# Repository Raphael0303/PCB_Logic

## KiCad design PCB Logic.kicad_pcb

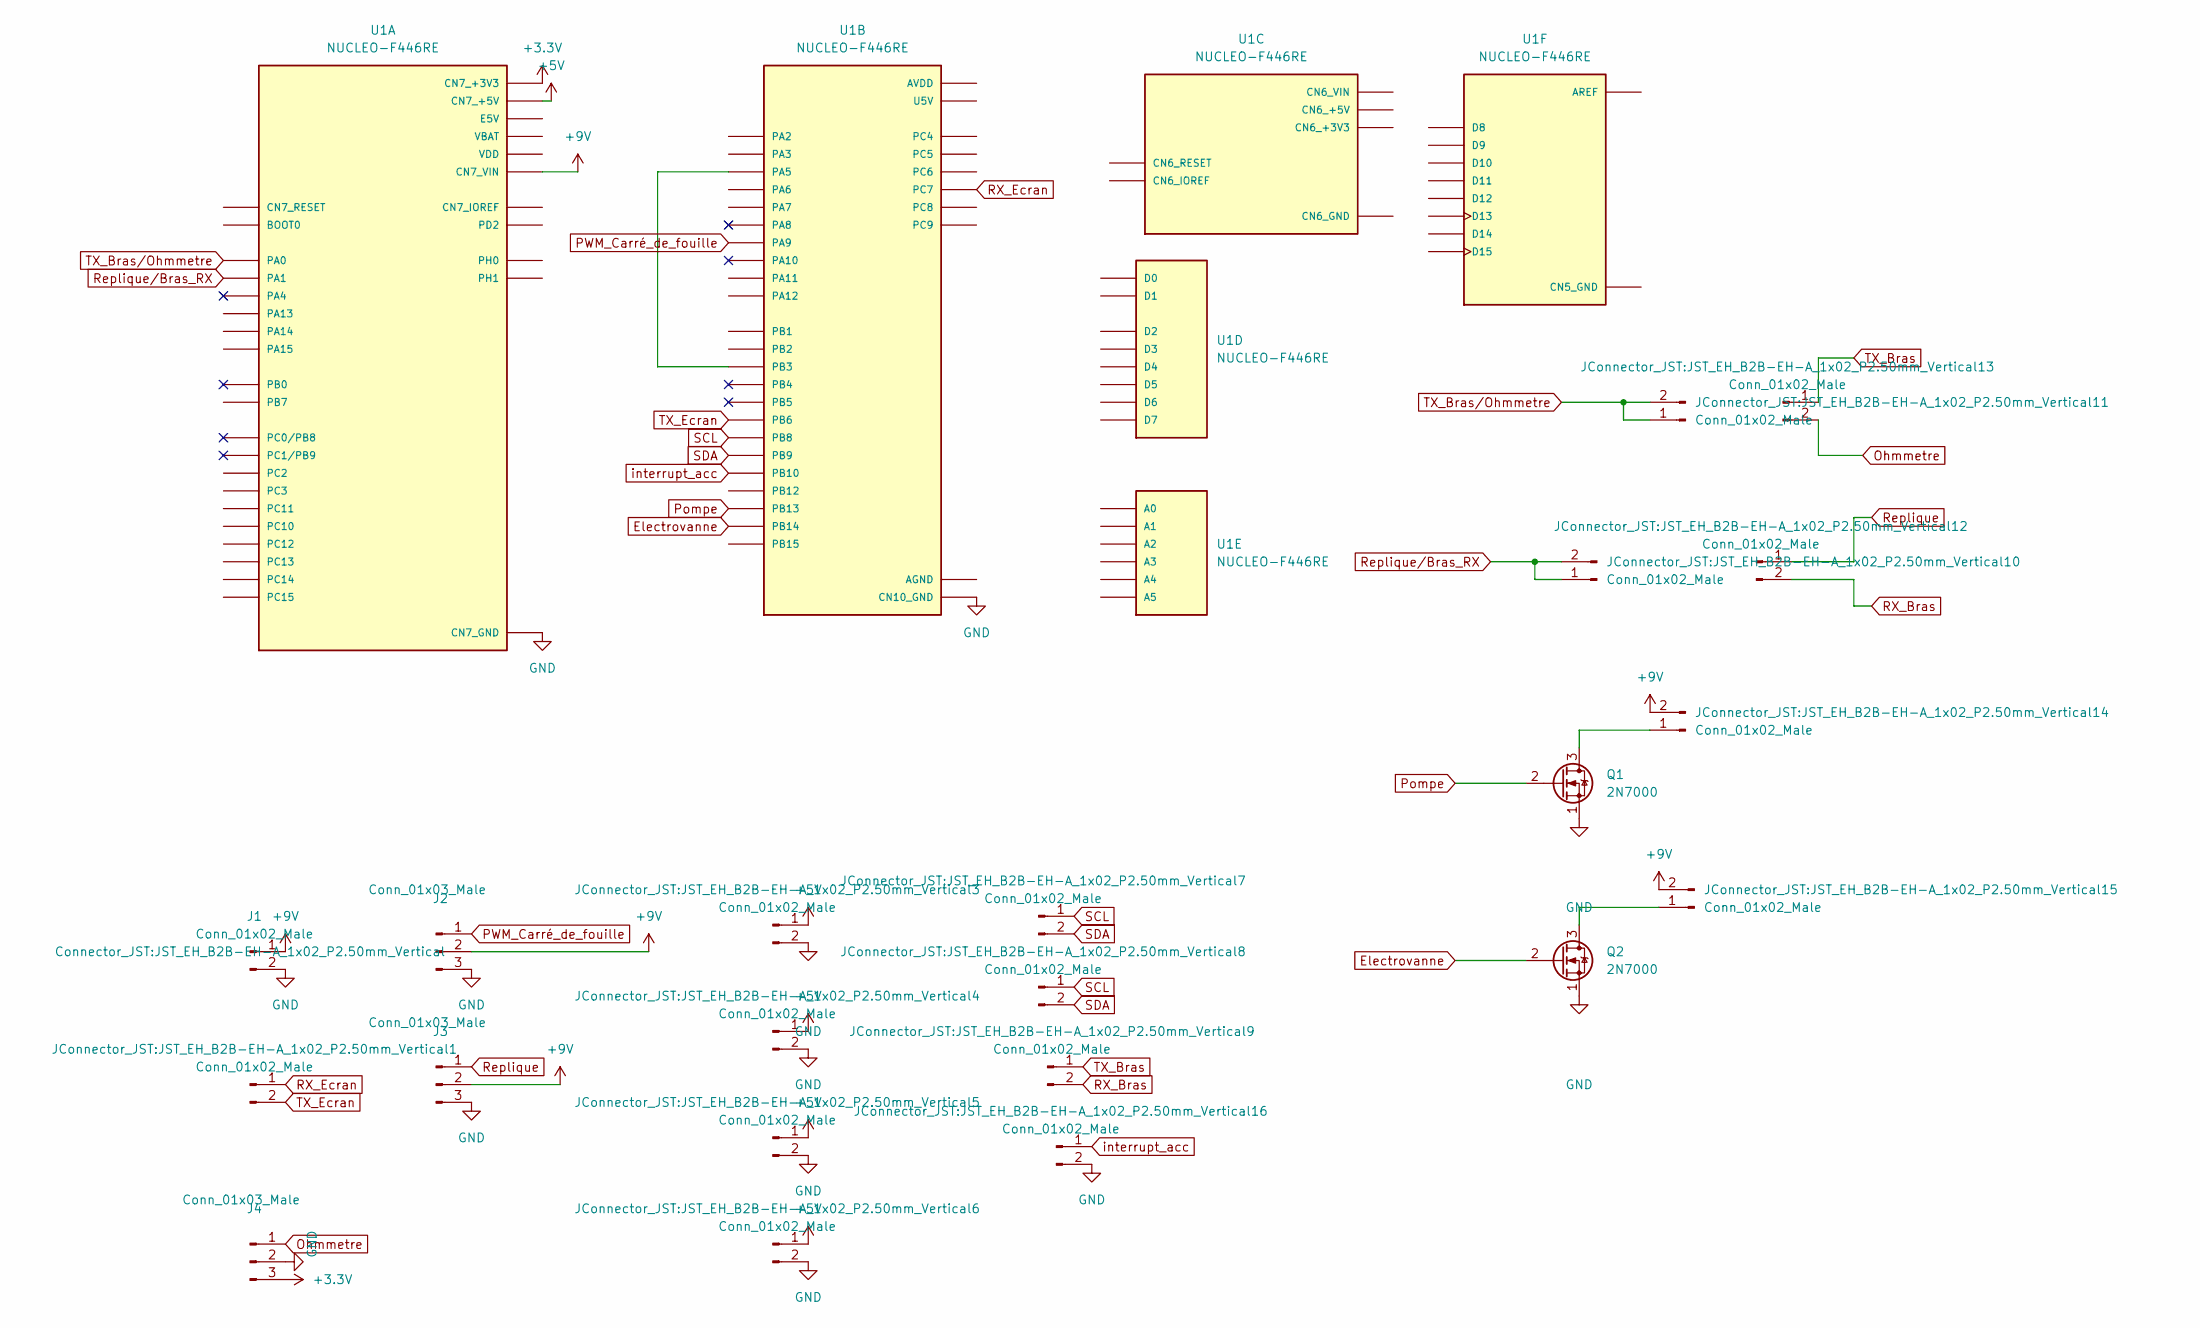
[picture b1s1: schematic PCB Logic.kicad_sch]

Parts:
J1: Conn_01x02_Male; JST_EH_B2B-EH-A_1x02_P2.50mm_Vertical
J2, J3, J4: Conn_01x03_Male; JST_EH_B3B-EH-A_1x03_P2.50mm_Vertical
JConnector_JST:JST_EH_B2B-EH-A_1x02_P2.50mm_Vertical1, JConnector_JST:JST_EH_B2B-EH-A_1x02_P2.50mm_Vertical3, JConnector_JST:JST_EH_B2B-EH-A_1x02_P2.50mm_Vertical4, JConnector_JST:JST_EH_B2B-EH-A_1x02_P2.50mm_Vertical5, JConnector_JST:JST_EH_B2B-EH-A_1x02_P2.50mm_Vertical6, JConnector_JST:JST_EH_B2B-EH-A_1x02_P2.50mm_Vertical7, JConnector_JST:JST_EH_B2B-EH-A_1x02_P2.50mm_Vertical8, JConnector_JST:JST_EH_B2B-EH-A_1x02_P2.50mm_Vertical9, JConnector_JST:JST_EH_B2B-EH-A_1x02_P2.50mm_Vertical14, JConnector_JST:JST_EH_B2B-EH-A_1x02_P2.50mm_Vertical15, JConnector_JST:JST_EH_B2B-EH-A_1x02_P2.50mm_Vertical16: Conn_01x02_Male; JST_EH_B2B-EH-A_1x02_P2.50mm_Vertical
JConnector_JST:JST_EH_B2B-EH-A_1x02_P2.50mm_Vertical10, JConnector_JST:JST_EH_B2B-EH-A_1x02_P2.50mm_Vertical11, JConnector_JST:JST_EH_B2B-EH-A_1x02_P2.50mm_Vertical12, JConnector_JST:JST_EH_B2B-EH-A_1x02_P2.50mm_Vertical13: Conn_01x02_Male; PinHeader_1x02_P2.54mm_Vertical
Q1, Q2: 2N7000; TO-220-3_Vertical
U1: NUCLEO-F446RE; MODULE_NUCLEO-F446RE; PARTREV 13

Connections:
+3V3: J4.3, U1.CN7_16 (CN7_+3V3); also elsewhere on the board
+5V: JConnector_JST:JST_EH_B2B-EH-A_1x02_P2.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.1, JConnector_JST:JST_EH_B2B-EH-A_1x02_P2.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.1, JConnector_JST:JST_EH_B2B-EH-A_1x02_P2.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.1, JConnector_JST:JST_EH_B2B-EH-A_1x02_P2.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.1, U1.CN7_18 (CN7_+5V)
+9V: J1.1, J2.2, J3.2, JConnector_JST:JST_EH_B2B-EH-A_1x02_P2.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.2, JConnector_JST:JST_EH_B2B-EH-A_1x02_P2.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.2, U1.CN7_24 (CN7_VIN)
Electrovanne: Q2.2 (G), U1.CN10_28 (PB14)
GND: J1.2, J2.3, J3.3, J4.2, JConnector_JST:JST_EH_B2B-EH-A_1x02_P2.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.2, JConnector_JST:JST_EH_B2B-EH-A_1x02_P2.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.2, JConnector_JST:JST_EH_B2B-EH-A_1x02_P2.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.2, JConnector_JST:JST_EH_B2B-EH-A_1x02_P2.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.2, JConnector_JST:JST_EH_B2B-EH-A_1x02_P2.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.2, Q1.1 (S), Q2.1 (S), U1.CN7_8 (CN7_GND), U1.CN7_19 (CN7_GND), U1.CN7_20 (CN7_GND), U1.CN7_22 (CN7_GND), U1.CN10_9 (CN10_GND), U1.CN10_20 (CN10_GND); also elsewhere on the board
unnamed: JConnector_JST:JST_EH_B2B-EH-A_1x02_P2.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.1, Q1.3 (D)
unnamed: JConnector_JST:JST_EH_B2B-EH-A_1x02_P2.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.1, Q2.3 (D)
unnamed: U1.CN6_6 (CN6_GND), U1.CN6_7 (CN6_GND)
unnamed: U1.CN10_11 (PA5), U1.CN10_31 (PB3)
Ohmmetre: J4.1, JConnector_JST:JST_EH_B2B-EH-A_1x02_P2.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.2
PWM_Carré_de_fouille: J2.1, U1.CN10_21 (PA9)
Pompe: Q1.2 (G), U1.CN10_30 (PB13)
RX_Bras: JConnector_JST:JST_EH_B2B-EH-A_1x02_P2.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.2, JConnector_JST:JST_EH_B2B-EH-A_1x02_P2.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.2
RX_Ecran: JConnector_JST:JST_EH_B2B-EH-A_1x02_P2.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.1, U1.CN10_19 (PC7)
Replique: J3.1, JConnector_JST:JST_EH_B2B-EH-A_1x02_P2.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.1
Replique/Bras_RX: JConnector_JST:JST_EH_B2B-EH-A_1x02_P2.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.1, JConnector_JST:JST_EH_B2B-EH-A_1x02_P2.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.2, U1.CN7_30 (PA1)
SCL: JConnector_JST:JST_EH_B2B-EH-A_1x02_P2.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.1, JConnector_JST:JST_EH_B2B-EH-A_1x02_P2.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.1, U1.CN10_3 (PB8)
SDA: JConnector_JST:JST_EH_B2B-EH-A_1x02_P2.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.2, JConnector_JST:JST_EH_B2B-EH-A_1x02_P2.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.2, U1.CN10_5 (PB9)
TX_Bras: JConnector_JST:JST_EH_B2B-EH-A_1x02_P2.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.1, JConnector_JST:JST_EH_B2B-EH-A_1x02_P2.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.1
TX_Bras/Ohmmetre: JConnector_JST:JST_EH_B2B-EH-A_1x02_P2.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.1, JConnector_JST:JST_EH_B2B-EH-A_1x02_P2.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.2, U1.CN7_28 (PA0)
TX_Ecran: JConnector_JST:JST_EH_B2B-EH-A_1x02_P2.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.2, U1.CN10_17 (PB6)
interrupt_acc: JConnector_JST:JST_EH_B2B-EH-A_1x02_P2.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.1, U1.CN10_25 (PB10)

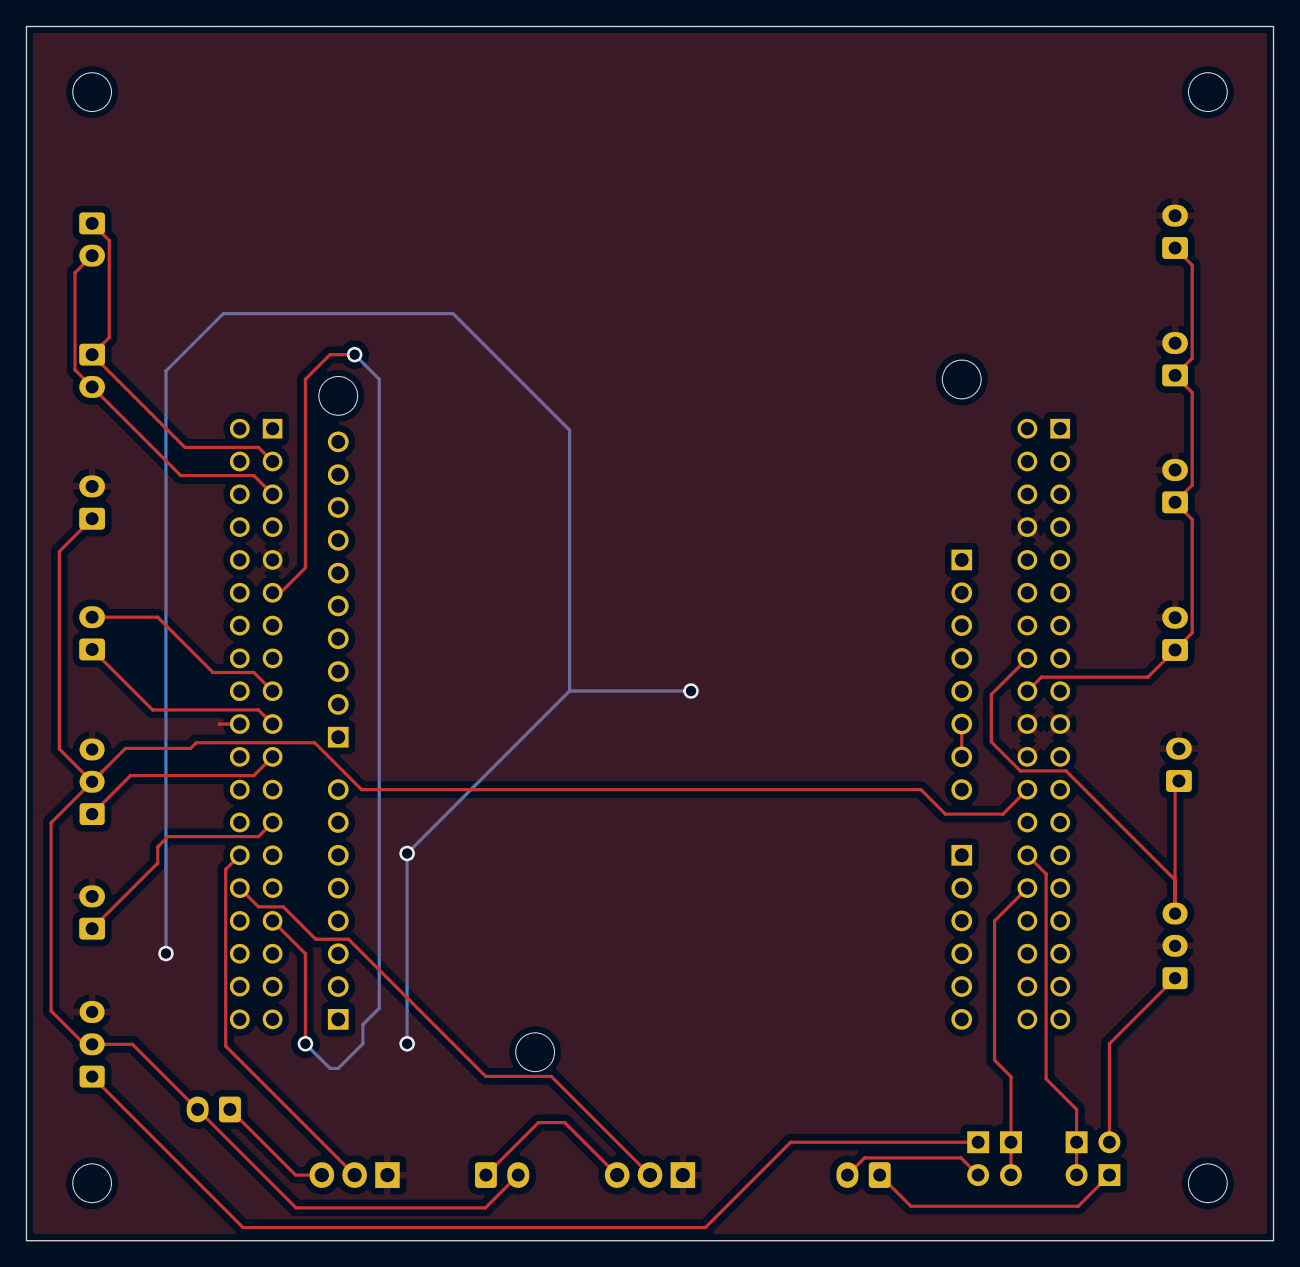
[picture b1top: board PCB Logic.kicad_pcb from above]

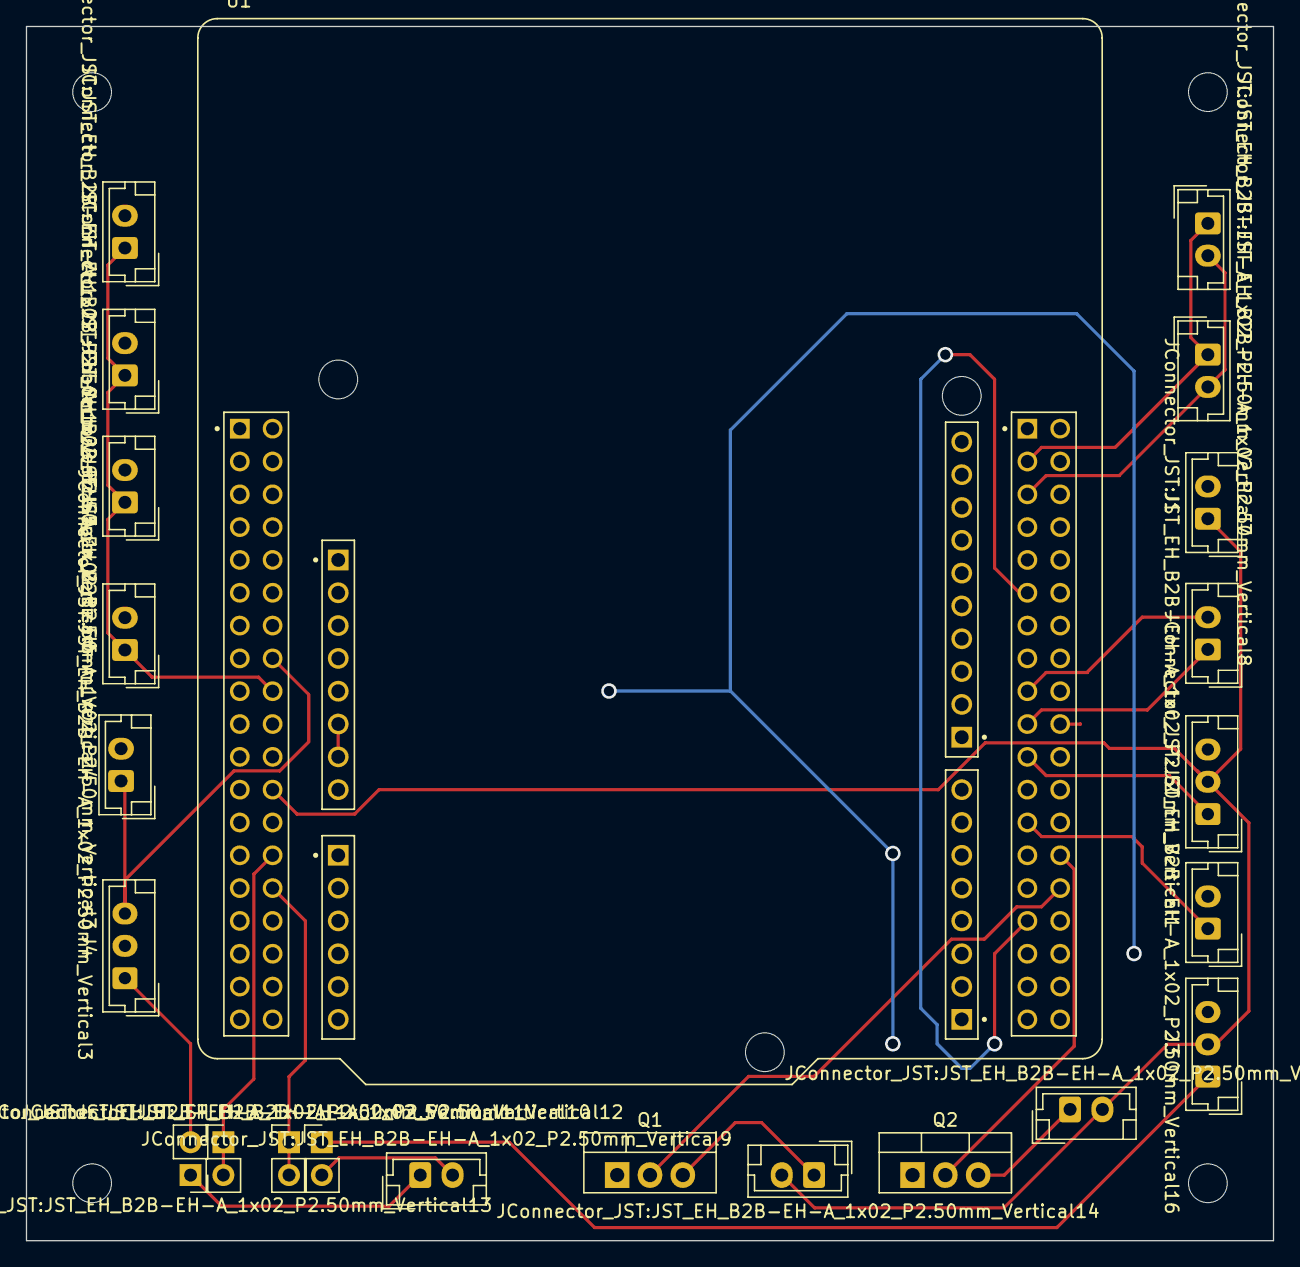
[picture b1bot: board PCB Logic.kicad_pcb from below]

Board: 2 copper layers, 96.5 x 94.0 mm, 23 parts (23 on the bottom side), 22 nets.

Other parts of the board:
JConnector_JST:JST_EH_B2B-EH-A_1x02_P2.50mm_Vertical3#2: Conn_01x02_Male; JST_EH_B2B-EH-A_1x02_P2.50mm_Vertical

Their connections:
+3V3: JConnector_JST:JST_EH_B2B-EH-A_1x02_P2.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.1; also elsewhere on the board
GND: JConnector_JST:JST_EH_B2B-EH-A_1x02_P2.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.2; also elsewhere on the board

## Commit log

2022-09-22 start
